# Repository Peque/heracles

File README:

Developent of the Heracles robot.

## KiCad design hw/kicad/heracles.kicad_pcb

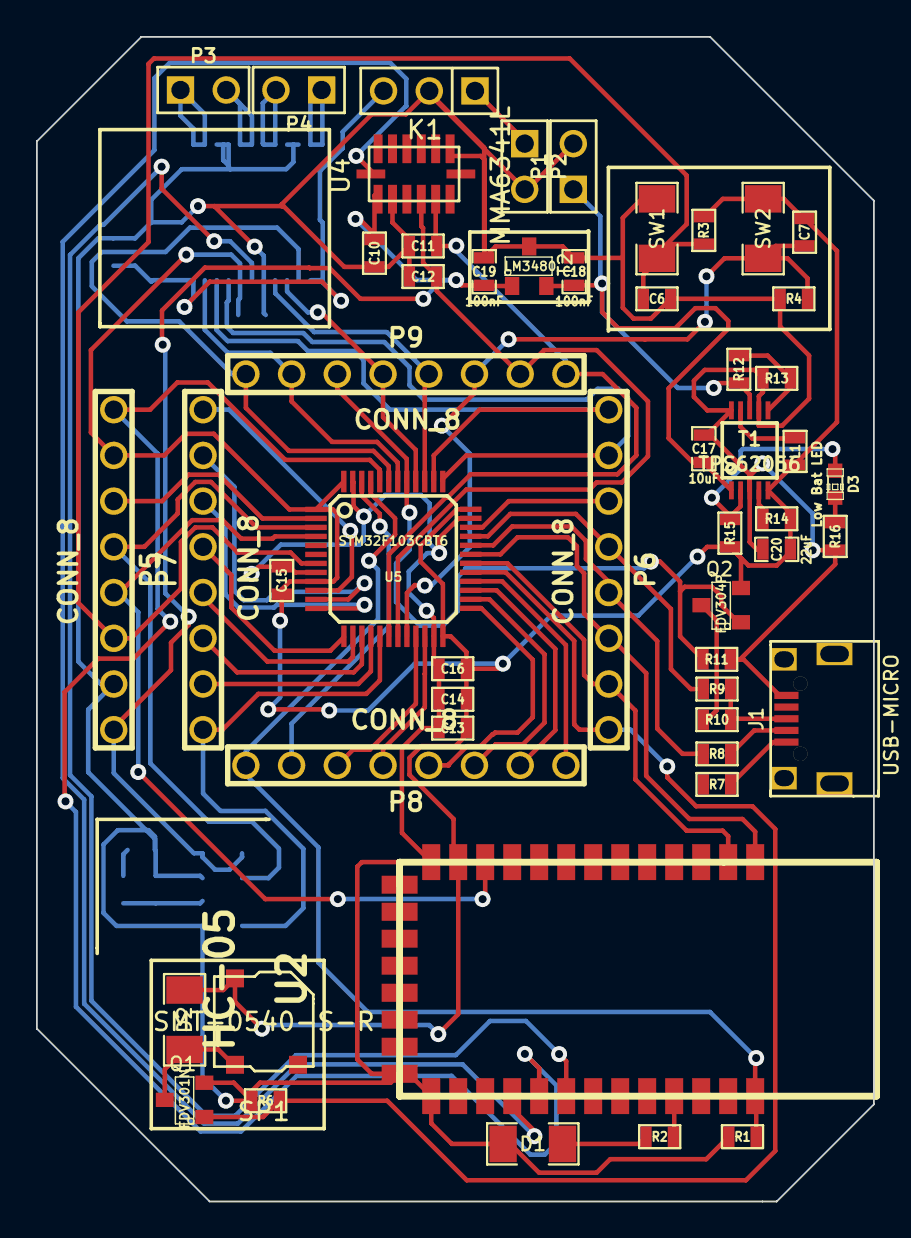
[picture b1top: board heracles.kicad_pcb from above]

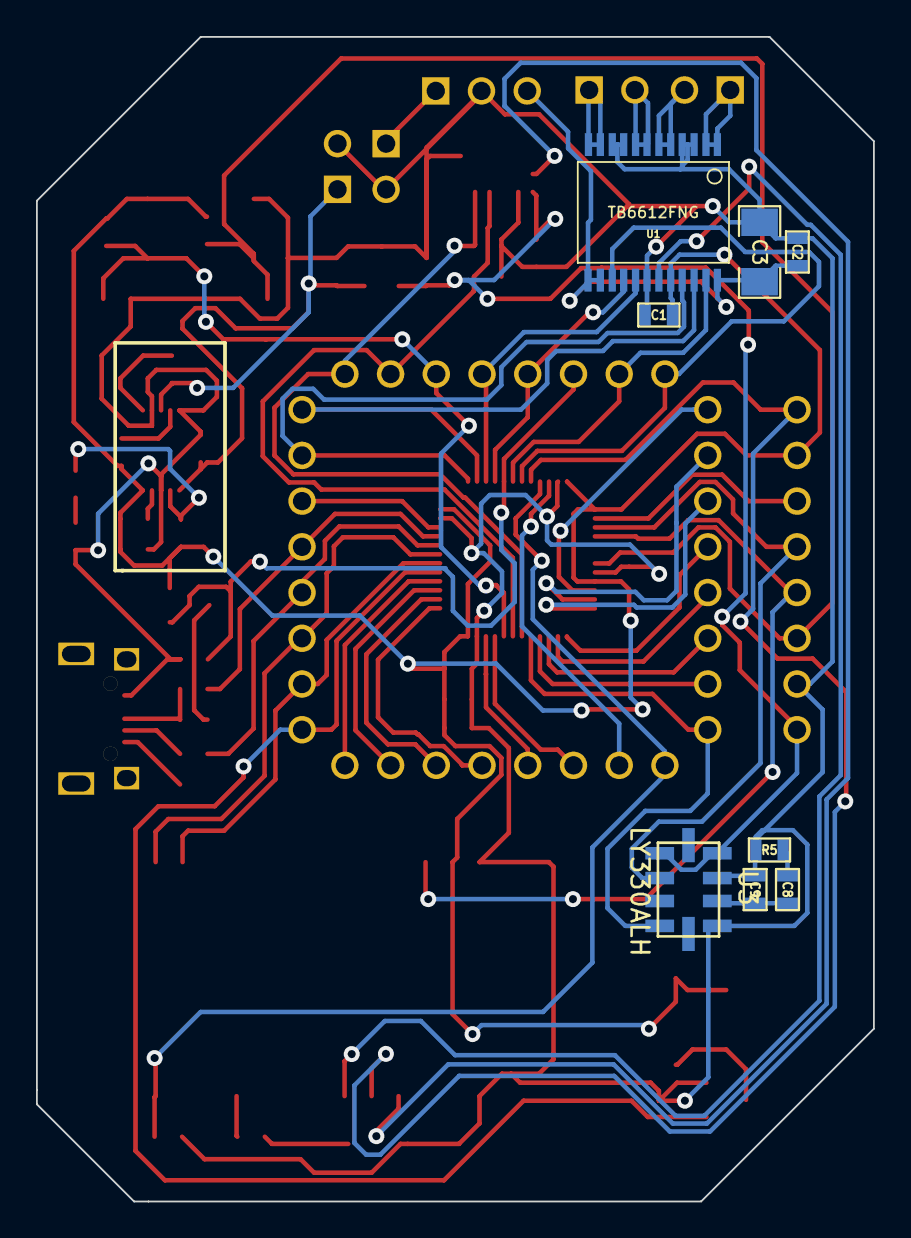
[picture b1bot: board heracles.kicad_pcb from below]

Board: 2 copper layers, 46.5 x 64.7 mm, 61 parts (8 on the bottom side), 63 nets.

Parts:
C1, C2: 0.1uF; SM0603
C3: 10uF , 20V; SM1206
C6, C7, C13, C14, C15, C16: 100nF; SM0603
C8: 470nF; SM0603
C9: 10nF; SM0603
C10, C11, C12: 3.3nF; SM0603
C17: 10uF; SM0603_Capa
C18, C19: 100nF; SM0603_Capa
C20: 22uF; SM0603_Capa
D1: Work mode LED; SM1206
D2: DIODE; SM1206
D3: Low Bat LED; LED-0603
J1: USB-MICRO; MICRO_USB
K1: MOTOR_CONV; PIN_ARRAY_3X1
L1: 10uF; SM0603
P1: LOGIC_BAT; PIN_ARRAY_2X1
P2: MOTOR_BAT; PIN_ARRAY_2X1
P3: MOTOR_A; PIN_ARRAY_2X1
P4: MOTOR_B; PIN_ARRAY_2X1
P5, P6, P7, P8, P9: CONN_8; pin_array_8
Q1: FDV301N; SOT-23_MOS
Q2: FDV304P; SOT-23_MOS
R1: 100K; SM0603
R2, R16: 470; SM0603
R3, R4, R13: 100k; SM0603
R5, R11: 10k; SM0603
R6: 47k; SM0603
R7, R8, R9: 22; SM0603
R10: 1.5k; SM0603
R12: 180k; SM0603
R14, R15: 1M; SM0603
SP1: SMT-0540-S-R
SW1, SW2: B3U-1000P; SM1206
T1: TPS62056; MSOP10-0.5
T2: LM3480; SOT23
U1: TB6612FNG; SSOP24-P-300.0.65A
U2: HC-05; HC-0X
U3: LY330ALH
U4: MMA6341L
U5: STM32F103CBT6; LQFP48

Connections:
/Accelerometer/3V3: C10.2, C19.1, P5.8, T2.1, U3.1, U3.9, U4.6
/Bluetooth/AT_MODE: P8.8, R1.1, U2.34, U5.45
/Bluetooth/PIO2: U2.25, U4.7
/Bluetooth/PIO4: U1.19, U2.27
/Buttons/~RST: C6.1, P5.6, R3.2, SW1.1, U5.7
/Gyroscope/OUTZ: P7.1, U3.6, U5.17
/M_VIN: K1.1, P2.1
/Microcontroller/AV-: C1.2, C2.2, C3.2, C6.2, C9.2, C10.1, C11.2, C12.2, C13.2, C14.2, C15.2, C16.2, C17.2, C18.2, C19.2, C20.2, D1.2, J1.5, K1.2, P1.2, P2.2, P5.7, Q1.S, R1.2, R4.2, R5.2, R6.2, R11.1, R13.2, R16.2, SW1.2, T1.3, T1.7, T1.10, T2.3, U1.3, U1.4, U1.9, U1.10, U1.18, U2.13, U2.21, U2.22, U3.2, U3.4, U4.5, U4.13, U5.8, U5.23, U5.35, U5.47
/Microcontroller/BOOT0: P5.1, U2.26, U5.44
/Microcontroller/PA0-WKUP: P7.8, U5.10
/Microcontroller/PA1: P7.7, U5.11
/Microcontroller/PA2: P7.6, U5.12
/Microcontroller/PA3: P7.5, U5.13
/Microcontroller/PA4: P7.4, U5.14
/Microcontroller/PA5: P7.3, U5.15
/Microcontroller/PA6: P7.2, U5.16
/Microcontroller/PA8: P6.8, Q1.G, R6.1, U5.29
/Microcontroller/PA9: P6.7, U2.2, U5.30
/Microcontroller/PA10: P6.6, U2.1, U5.31
/Microcontroller/PA11: P6.5, R8.2, U5.32
/Microcontroller/PA12: P6.4, R9.2, U5.33
/Microcontroller/PA13: P6.3, U5.34
/Microcontroller/PB0: C11.1, P9.8, U4.2, U5.18
/Microcontroller/PB1: C12.1, P9.7, U4.3, U5.19
/Microcontroller/PB2-BOOT1: C7.2, P9.6, R4.1, SW2.2, U5.20
/Microcontroller/PB5: P9.3, Q2.G, R11.2, U5.41
/Microcontroller/PB6: P9.2, U1.23, U5.42
/Microcontroller/PB7: P9.1, U1.15, U5.43
/Microcontroller/PB9: P8.7, U5.46
/Microcontroller/PB10: P8.6, U5.21
/Microcontroller/PB11: P8.5, U5.22
/Microcontroller/PB12: P8.4, U5.25
/Microcontroller/PB13: P8.3, U5.26
/Microcontroller/PB14: P8.2, U5.27
/Microcontroller/PB15: P8.1, U5.28
/Microcontroller/PC13-TAMPER-RTC: P5.3, U5.2
/Microcontroller/PC14-OSC32_IN: P5.4, U3.8, U5.3
/Microcontroller/PC15-OSC32_OUT: P5.5, U2.11, U5.4
/Motor driver/AIN1: P6.2, U1.21, U5.37
/Motor driver/AIN2: P6.1, U1.22, U5.38
/Motor driver/AO1: P3.1, U1.1, U1.2
/Motor driver/AO2: P3.2, U1.5, U1.6
/Motor driver/BIN1: P9.5, U1.17, U5.39
/Motor driver/BIN2: P9.4, U1.16, U5.40
/Motor driver/BO1: P4.1, U1.11, U1.12
/Motor driver/BO2: P4.2, U1.7, U1.8
/Motor driver/VMOT: C2.1, C3.1, K1.3, U1.13, U1.14, U1.24
/Power/LB: D3.1, R15.2, T1.2
/Power/PG: R14.2, T1.4
/Power/VIN: C17.1, C18.1, P1.1, R12.1, T1.1, T1.8, T2.2
/Usb/3.3V: C1.1, C7.1, C13.1, C14.1, C15.1, C16.1, C20.1, D2.2, L1.2, P5.2, Q2.S, R3.1, R14.1, R15.1, SP1.1, SW2.1, T1.5, U1.20, U2.12, U5.1, U5.9, U5.24, U5.36, U5.48
/Usb/VUSB: J1.1, R7.1
unnamed: R2.1, U2.31
unnamed: D1.1, R2.2
unnamed: C8.1, C9.1, U3.3
unnamed: C8.2, R5.1
unnamed: D2.1, Q1.D, SP1.2
unnamed: R12.2, R13.1, T1.6
unnamed: D3.2, R16.1
unnamed: L1.1, T1.9
unnamed: J1.2, R8.1
unnamed: J1.3, R9.1, R10.1
unnamed: Q2.D, R10.2

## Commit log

2013-04-22 Initial main.c file
2013-08-01 Added initial documentation
2013-08-19 Added bluetooth, motor driver and external ocillator circuits
2013-08-22 Added buttons circuit
2013-08-22 For now (while prototyping), we'll be using 1206 LEDs instead of smaller packages
2013-08-22 Added LY330ALH gyroscope to the Reset's schematics library
2013-08-22 Added gyroscope circuit
2013-08-22 Fixed bad pin name in STM32F103CBT6 footprint
2013-08-22 Modified a pair of labels in STM32F103CBT6 schematic component
2013-08-22 Added microcontroller circuit
2013-08-22 Added title and version to the main sheet
2013-08-24 Added SMT-0540-S-R speaker to Reset's components library
2013-08-24 Added speaker circuit
2013-08-24 Using a more convenient (and cheaper) N-channel MOSFET for the speaker, simplified speaker design
2013-08-24 Added MMA6341L 2-axis accelerometer to Reset's components library
2013-08-24 Added accelerometer circuit
2013-08-24 Placed a missing no-connect flag in the speaker circuit
2013-08-24 Added missing footprint for the accelerometer
2013-08-24 Added missing junction in speaker's schematic
2013-08-25 Zener diode changed to schottky diode in buzzer schematic
2013-09-05 Replaced schottky diode with a regular diode in the buzzer schematic
2013-12-13 Added usb circuit
2013-12-13 Fixed project to show usb schematic
2013-12-13 Added TPS62056 component to reset library
2013-12-13 Fixed TPS62056 pins
2013-12-14 Rearranged TPD62056 pins for better schematic composition
2013-12-14 Added power schematic
2014-01-24 Microcontroller pins assigned to module pins
    Added a Low Battery LED and a 3V3 linear regulator for powering analogic
    devices
2014-02-20 Added missing footprints
2014-02-20 Added micro-usb footprint
2014-02-24 Changed labels for BT AT-mode pin and speaker VCC pin
2014-03-13 Removed oscillator schematic. Added pin arrays for debugging
2014-03-14 Fixed some schematic and library bugs
2014-03-14 Added PCB circuit
2014-03-14 Separate analog and digital power in the uC
2014-03-15 Added script to connect the computer's bluetooth
2014-03-30 Fixed MMA6341L footprint from kicad offset bug
2014-03-30 Removed offset dependency from LY330ALH footprint
2014-03-30 Added some missing connections in pcb
2014-03-30 Fixed Q1 and Q2 footprints
2014-03-30 Updated micro USB footprint
2014-03-30 Added PCB edges
2014-03-31 Removed unnecessary backup file
2014-03-31 Updated .gitignore file
2014-03-31 Added board dimensions
2014-04-01 Fixed missing holes
